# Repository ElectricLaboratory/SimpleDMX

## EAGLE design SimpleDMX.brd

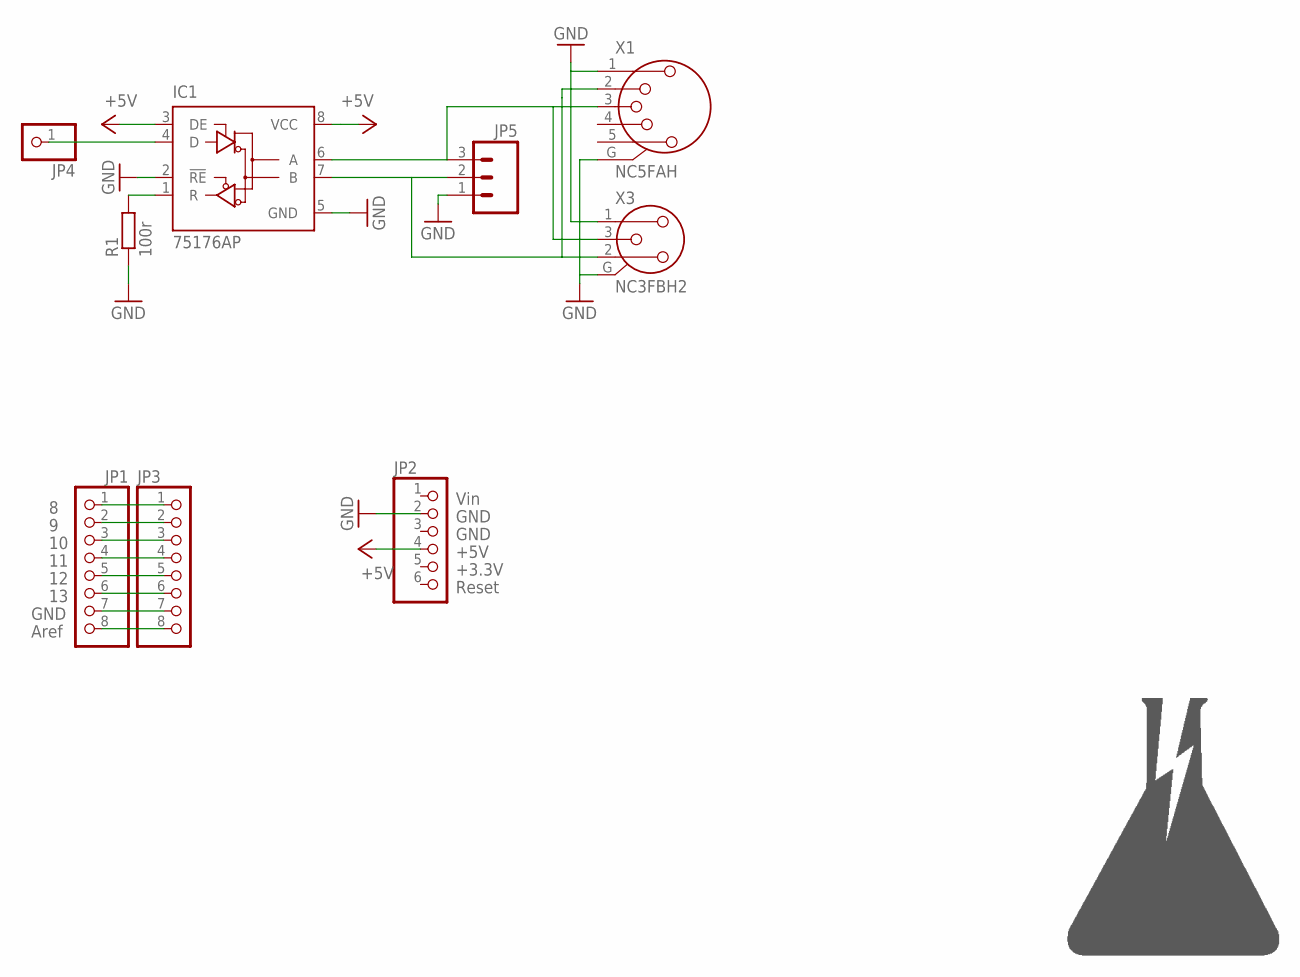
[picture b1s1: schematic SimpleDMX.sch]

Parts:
IC1: 75176AP; DIL08
JP1, JP3: PINHD-1X8BIG; 1X08-BIG
JP2: PINHD-1X6B; 1X06-BIG
JP4: PINHD-1X1; 1X01
JP5: M03SCREW; SCREWTERMINAL-3.5MM-3
R1: 100r; 0207/7
U$1: EL-LOGO
X1: NC5FAH
X3: NC3FBH2

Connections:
+5V: IC1.3 (DE), IC1.8 (VCC), JP2.4
GND: IC1.2 (!RE), IC1.5 (GND), JP2.2, JP5.1, R1.1, X1.1, X1.G, X3.1, X3.G
unnamed: JP1.1, JP3.1
unnamed: JP1.2, JP3.2
unnamed: JP1.3, JP3.3
unnamed: JP1.4, JP3.4
unnamed: JP1.5, JP3.5
unnamed: JP1.6, JP3.6
unnamed: JP1.7, JP3.7
unnamed: JP1.8, JP3.8
unnamed: IC1.1 (R), R1.2
unnamed: IC1.4 (D), JP4.1
unnamed: IC1.6 (A), JP5.3, X1.3, X3.3
unnamed: IC1.7 (B), JP5.2, X1.2, X3.2

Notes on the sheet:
GND
Aref
Vin
+5V
+3.3V
Reset

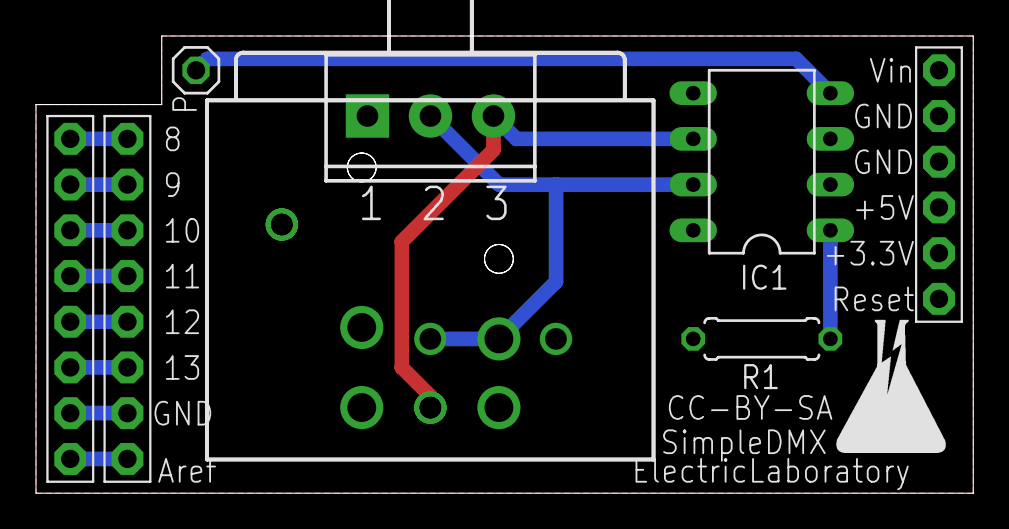
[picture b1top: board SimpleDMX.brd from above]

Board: 2 copper layers, 52.1 x 25.4 mm, 10 parts (0 on the bottom side), 14 nets.

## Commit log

2013-06-15 Add PDFs

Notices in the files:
SimpleDMX.brd:
CC-BY-SA
parts and their libraries:
SparkFun-Connectors: Licensing: CC v3.0 Share-Alike You are welcome to use this library for commercial purposes.
